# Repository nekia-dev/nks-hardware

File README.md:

# NkS — Placa portadora (carrier) · PROYECTO SOMNIA

**Nekia Systems S.L.** · Hardware del monitor de sueño NkS
*"Your Data, Your Device."*

Placa portadora para ESP32-S3 DevKitC-1 N16R8. Diseño "árbol de pascua apagado":
hardware mínimo, el valor está en el software.

---

## Estado

| Etapa | Estado |
|---|---|
| Hardware congelado | ✅ |
| Esquemático + ERC | ✅ 0 errores |
| Layout + DRC | ✅ 0 errores / 0 sin conectar |
| Gerbers | ✅ generados y verificados |
| Fabricación | ⏳ pendiente de pedido |
| Validación física | ⏳ pendiente (ver §Validación) |

---

## Datos de fabricación

| Parámetro | Valor |
|---|---|
| Dimensiones | **80 × 90 mm** (8 × 9 cm) |
| Capas | 2 (F.Cu / B.Cu) |
| Grosor | 1,6 mm (estándar) |
| Contorno | Rectangular |
| Plano de masa | GND en **ambas** caras |
| Pistas | 271 segmentos + 4 vías |
| Taladros | 80 (brocas 0,3 / 1,0 / 1,1 mm) |
| Ancho de pista | 0,2 mm (señal) |
| Componentes | 18 |

> El formato circular queda aplazado: el rectangular abarata el prototipo.

---

## Arquitectura

El ESP32-S3 DevKitC-1 **no va soldado**: se enchufa sobre dos tiras de pines
hembra 1×22 (`J2` = fila J1 del DevKit, `J3` = fila J3). Los sensores y
periféricos son módulos comerciales (breakouts) montados sobre headers.

**Consecuencia:** el fabricante entrega la placa **desnuda**. El montaje
(soldadura de headers y pasivos + enchufar el DevKit) es manual.

---

## Pinout congelado

| Bus | Señal | GPIO | Posición en header |
|---|---|---|---|
| I2S | WS | 11 | J2 pos. 17 |
| I2S | SCK | 12 | J2 pos. 18 |
| I2S | SD | 13 | J2 pos. 19 |
| SPI | MOSI | 15 | J2 pos. 8 |
| SPI | MISO | 16 | J2 pos. 9 |
| SPI | SCLK | 17 | J2 pos. 10 |
| SPI | CS | 18 | J2 pos. 11 |
| I2C | SDA | 8 | J2 pos. 12 |
| I2C | SCL | 9 | J2 pos. 15 |
| — | Botón on/off | 14 | J2 pos. 20 |
| — | LED estado | 21 | J3 pos. 18 |

**Alimentación:** 3V3 en J2 pos. 1–2 · GND en J2 pos. 22 y J3 pos. 1, 21, 22.

**Pines reservados (no usar):** strapping 0/3/45/46 · PSRAM octal (N16R8)
33–37 · USB nativo 19/20.

> El pinout físico J1/J3 procede de la guía oficial de Espressif del
> ESP32-S3-DevKitC-1 v1.1. **Verificar contra la placa real antes de soldar**
> (ver §Validación).

---

## BOM

| Ref | Componente | Interfaz | Notas |
|---|---|---|---|
| J2, J3 | Header 1×22 hembra ×2 | — | Zócalo del DevKit (paso 2,54 mm, filas a 22,86 mm) |
| A1 | INMP441 | I2S | Canal izquierdo — `L/R` → GND |
| A2 | INMP441 | I2S | Canal derecho — `L/R` → 3V3 |
| J1 | Lector microSD | SPI | — |
| U2 | RTC DS3231 + AT24C32 | I2C | 0x68 / 0x57 |
| U3 | SHT30 | I2C | 0x44 — temperatura + humedad |
| SW1 | Pulsador 6 mm | — | On/off, activo-bajo |
| R1 | 1 kΩ (0805) | — | Serie del LED |
| R2 | 10 kΩ (0805) | — | Pull-up del botón |
| D1 | LED (0805) | — | Indicador de estado |
| C1–C6 | 100 nF (0805) | — | Desacoplo + antirrebote |
| C7 | 10 µF (0805) | — | Bulk en el riel 3V3 |

**Aparte (no van en la placa):** ESP32-S3 DevKitC-1 N16R8, tarjeta microSD,
cable USB-C, carcasa.

Todas las huellas proceden de las **librerías estándar de KiCad**; el proyecto
no depende de librerías propias de footprints.

---

## Estructura del repositorio

```
nks.kicad_pro          Proyecto KiCad
nks.kicad_sch          Esquemático
nks.kicad_pcb          Placa (rutada, DRC limpio)
nks.kicad_sym          Biblioteca de símbolos del proyecto
sym-lib-table          Registro de la biblioteca de símbolos
docs/                  Informes de ingeniería
tools/nks-sch-gen/     Generador del esquemático en Rust
```

### Abrir el proyecto

Abrir `nks.kicad_pro` con **KiCad 10.0**. Los cuatro archivos de proyecto y
`sym-lib-table` deben estar en la misma carpeta.

---

## Validación (pendiente al recibir la placa)

El DRC a cero garantiza que la placa **coincide con el esquemático** y es
fabricable. **No** garantiza que el mapeo de pines del DevKit sea correcto.

1. **Continuidad con multímetro** (placa desnuda): comprobar que cada pad de
   los módulos pita con la posición esperada de J2/J3. Prioridad: I2C, I2S, SPI.
2. **Alimentación**: 3V3 y GND presentes en cada módulo antes de montar nada.
3. **Bloque a bloque**: alimentación → I2C (¿responde el RTC en 0x68?) → I2S →
   microSD. No montar todo de golpe.

---

## Decisiones de diseño registradas

- **2× INMP441 en estéreo** por el truco `L/R`: comparten los tres pines I2S sin
  GPIO adicionales. Habilita separar el ronquido propio del de la pareja.
- **SHT30 incorporado** como sensor de ambiente (temp + humedad). Restricción de
  layout: aislarlo térmicamente del DevKit y su regulador.
- **Sin conector USB-C propio**: se usa el USB-C nativo del DevKit.
- **BMP280 descartado**; **BH1750 aplazado**.
- **Plano de GND en ambas caras**: necesario porque D1 es SMD (su pad de masa
  vive solo en F.Cu) y el plano inferior quedó fragmentado por el rutado.

---

*Nekia Systems S.L. — CONFIDENCIAL*

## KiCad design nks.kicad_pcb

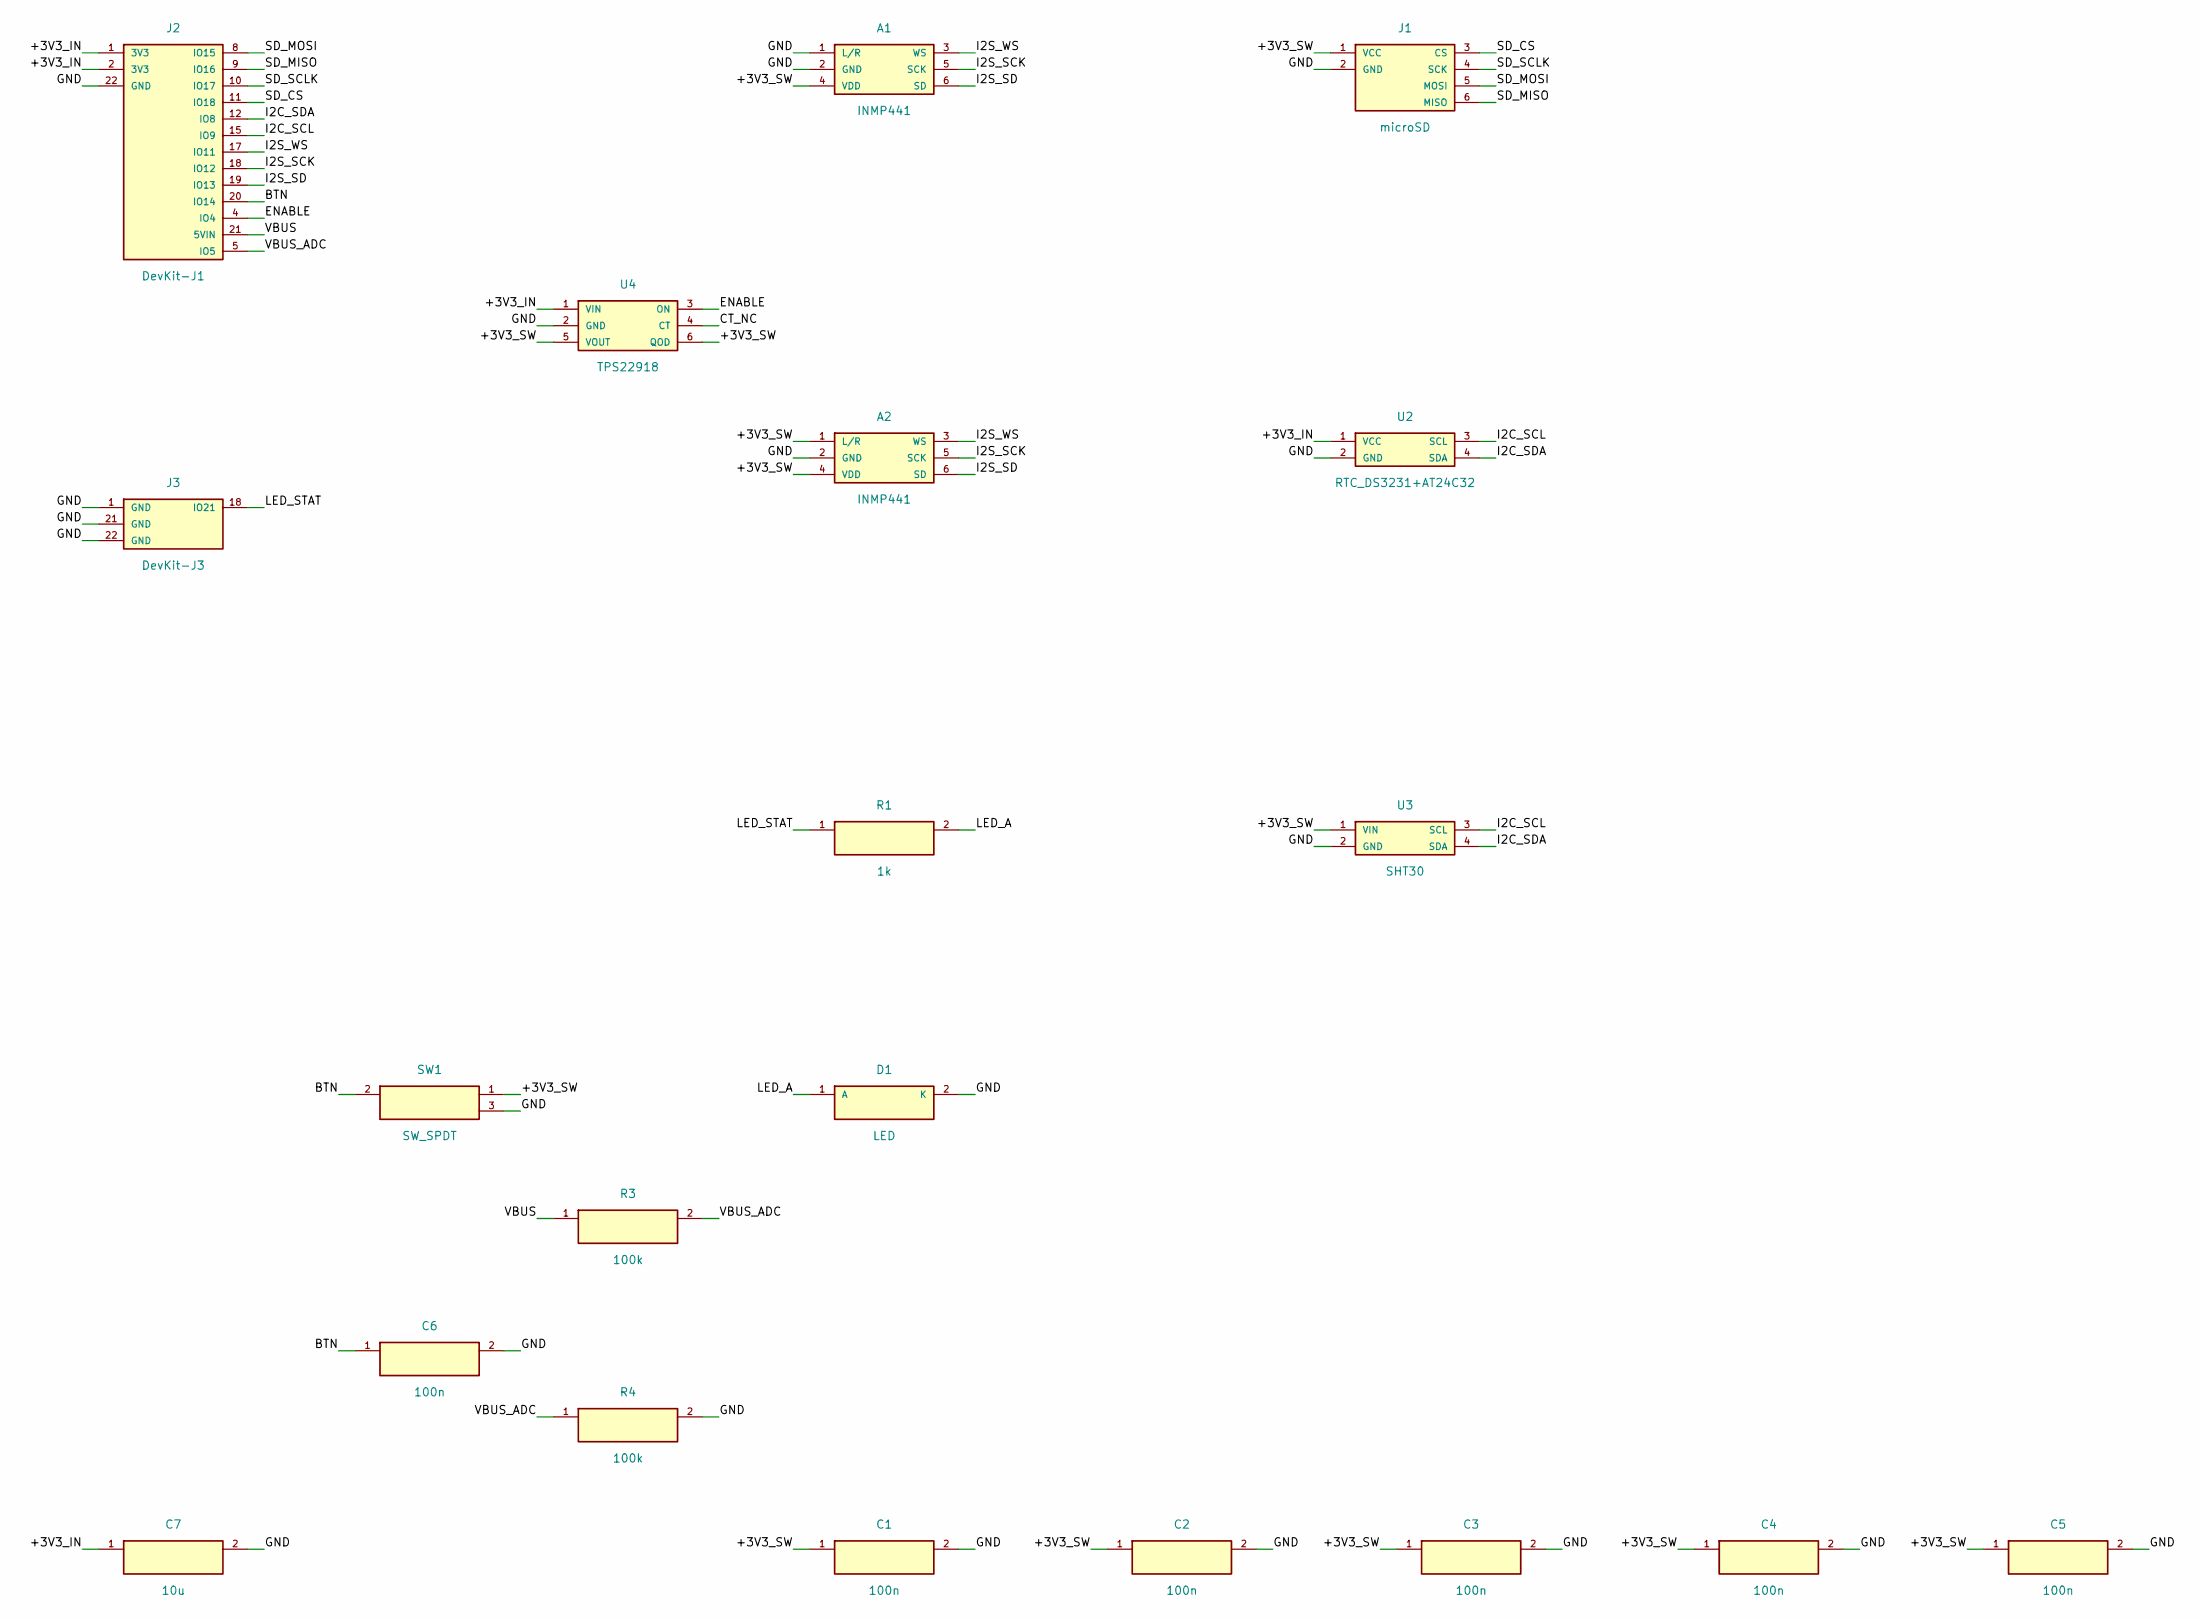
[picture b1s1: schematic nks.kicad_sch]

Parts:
A1, A2: INMP441; PinHeader_2x03_P2.54mm_Vertical
C1, C2, C3, C4, C5, C6: 100n; C_0805_2012Metric
C7: 10u; C_0805_2012Metric
D1: LED; LED_0805_2012Metric
J1: microSD; PinHeader_1x06_P2.54mm_Vertical
J2: DevKit-J1; PinHeader_1x22_P2.54mm_Vertical
J3: DevKit-J3; PinHeader_1x22_P2.54mm_Vertical
R1: 1k; R_0805_2012Metric
R3, R4: 100k; R_0805_2012Metric
SW1: SW_SPDT; SS12D00
U2: RTC_DS3231+AT24C32; PinHeader_1x06_P2.54mm_Vertical
U3: SHT30; PinHeader_1x04_P2.54mm_Vertical
U4: TPS22918; SOT-23-6

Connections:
/+3V3_IN: C7.1, J2.1 (3V3), J2.2 (3V3), U2.1 (VCC), U4.1 (VIN)
/+3V3_SW: A1.4 (VDD), A2.1 (L/R), A2.4 (VDD), C1.1, C2.1, C3.1, C4.1, C5.1, J1.1 (VCC), SW1.1, U3.1 (VIN), U4.5 (VOUT), U4.6 (QOD)
/BTN: C6.1, J2.20 (IO14), SW1.2
/CT_NC: U4.4 (CT)
/ENABLE: J2.4 (IO4), U4.3 (ON)
/GND: A1.1 (L/R), A1.2 (GND), A2.2 (GND), C1.2, C2.2, C3.2, C4.2, C5.2, C6.2, C7.2, D1.2 (K), J1.2 (GND), J2.22 (GND), J3.1 (GND), J3.21 (GND), J3.22 (GND), R4.2, SW1.3, U2.2 (GND), U3.2 (GND), U4.2 (GND)
/I2C_SCL: J2.15 (IO9), U2.3 (SCL), U3.3 (SCL)
/I2C_SDA: J2.12 (IO8), U2.4 (SDA), U3.4 (SDA)
/I2S_SCK: A1.5 (SCK), A2.5 (SCK), J2.18 (IO12)
/I2S_SD: A1.6 (SD), A2.6 (SD), J2.19 (IO13)
/I2S_WS: A1.3 (WS), A2.3 (WS), J2.17 (IO11)
/LED_A: D1.1 (A), R1.2
/LED_STAT: J3.18 (IO21), R1.1
/SD_CS: J1.3 (CS), J2.11 (IO18)
/SD_MISO: J1.6 (MISO), J2.9 (IO16)
/SD_MOSI: J1.5 (MOSI), J2.8 (IO15)
/SD_SCLK: J1.4 (SCK), J2.10 (IO17)
/VBUS: J2.21 (5VIN), R3.1
/VBUS_ADC: J2.5 (IO5), R3.2, R4.1

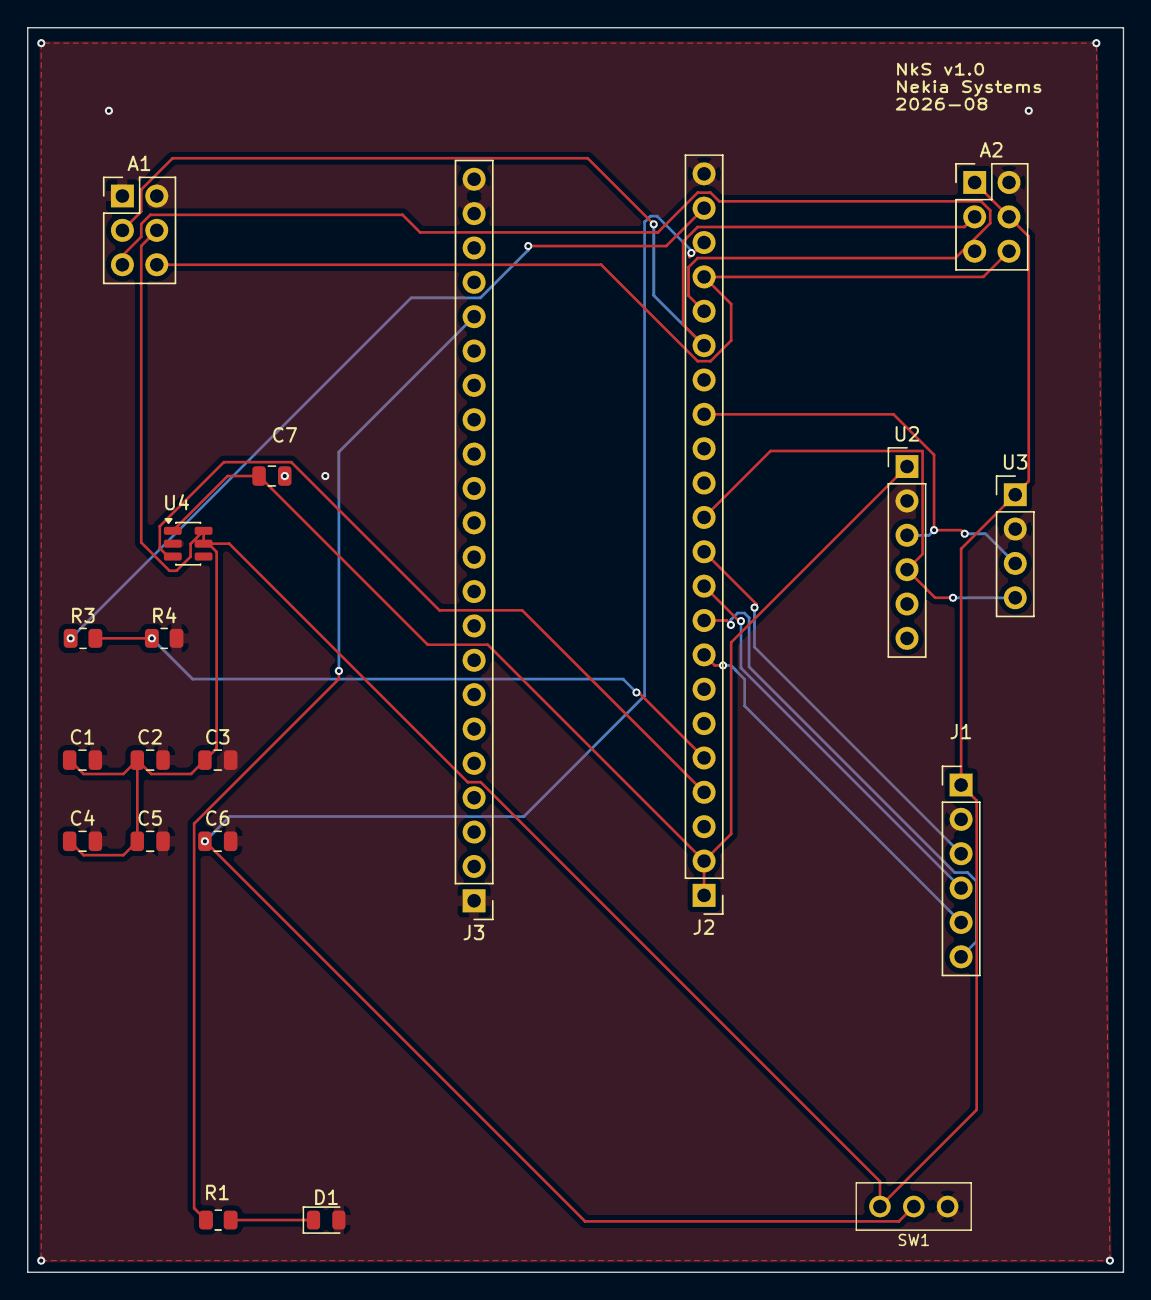
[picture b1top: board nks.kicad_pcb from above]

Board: 2 copper layers, 81.0 x 92.0 mm, 20 parts (0 on the bottom side), 18 nets.

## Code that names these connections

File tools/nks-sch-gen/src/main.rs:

mod kicad;
use kicad::{Component, Elec, Pin, Schematic, Side};

fn p_in(num: &str, name: &str, net: &str) -> Pin { Pin::new(num, name, Side::Left, Elec::PowerIn, net) }
fn p_out(num: &str, name: &str, net: &str) -> Pin { Pin::new(num, name, Side::Left, Elec::PowerOut, net) }
fn sig(num: &str, name: &str, net: &str) -> Pin { Pin::new(num, name, Side::Right, Elec::Passive, net) }
fn gpio(num: &str, name: &str, net: &str) -> Pin { Pin::new(num, name, Side::Right, Elec::Bidi, net) }
fn pas_l(num: &str, name: &str, net: &str) -> Pin { Pin::new(num, name, Side::Left, Elec::Passive, net) }
fn pas_r(num: &str, name: &str, net: &str) -> Pin { Pin::new(num, name, Side::Right, Elec::Passive, net) }

const HDR6: &str = "Connector_PinHeader_2.54mm:PinHeader_1x06_P2.54mm_Vertical";
const HDR4: &str = "Connector_PinHeader_2.54mm:PinHeader_1x04_P2.54mm_Vertical";
const HDR22: &str = "Connector_PinHeader_2.54mm:PinHeader_1x22_P2.54mm_Vertical";
const HDR2X3: &str = "Connector_PinHeader_2.54mm:PinHeader_2x03_P2.54mm_Vertical";
const R0805: &str = "Resistor_SMD:R_0805_2012Metric";
const C0805: &str = "Capacitor_SMD:C_0805_2012Metric";
const LED0805: &str = "LED_SMD:LED_0805_2012Metric";
const SW_SPDT: &str = "nks:SS12D00";
const SOT236: &str = "Package_TO_SOT_SMD:SOT-23-6";

fn main() {
    let mut sch = Schematic::new("NkS - SOMNIA carrier");

    // DevKit = two stock 1x22 female headers it plugs into. Pin NUMBER = physical
    // position on the official J1/J3 header (DevKitC-1 v1.1). One driver per rail
    // (3V3 + GND power_out, rest passive) to avoid multiple-power-output ERC errors.
    // J1 header row:
    sch.add(Component::new("J2", "DevKit-J1", HDR22, 20.0, 20.0)
        .pin(p_out("1", "3V3", "+3V3_IN")).pin(pas_l("2", "3V3", "+3V3_IN")).pin(p_out("22", "GND", "GND"))
        .pin(gpio("8", "IO15", "SD_MOSI")).pin(gpio("9", "IO16", "SD_MISO"))
        .pin(gpio("10", "IO17", "SD_SCLK")).pin(gpio("11", "IO18", "SD_CS"))
        .pin(gpio("12", "IO8", "I2C_SDA")).pin(gpio("15", "IO9", "I2C_SCL"))
        .pin(gpio("17", "IO11", "I2S_WS")).pin(gpio("18", "IO12", "I2S_SCK"))
        .pin(gpio("19", "IO13", "I2S_SD")).pin(gpio("20", "IO14", "BTN"))
        .pin(gpio("4", "IO4", "ENABLE"))
        .pin(gpio("21", "5VIN", "VBUS"))
        .pin(gpio("5", "IO5", "VBUS_ADC")));    // J3 header row:
    
    sch.add(Component::new("J3", "DevKit-J3", HDR22, 20.0, 90.0)
        .pin(pas_l("1", "GND", "GND")).pin(pas_l("21", "GND", "GND")).pin(pas_l("22", "GND", "GND"))
        .pin(gpio("18", "IO21", "LED_STAT")));

    // Load switch: parte +3V3_IN -> +3V3_SW, gobernado por ENABLE (GPIO4).
    sch.add(Component::new("U4", "TPS22918", SOT236, 90.0, 60.0)
        .pin(p_in("1", "VIN", "+3V3_IN")).pin(p_in("2", "GND", "GND"))
        .pin(sig("3", "ON", "ENABLE")).pin(sig("4", "CT", "CT_NC"))
        .pin(p_out("5", "VOUT", "+3V3_SW")).pin(sig("6", "QOD", "+3V3_SW")));

    sch.add(Component::new("A1", "INMP441", HDR2X3, 130.0, 20.0)
        .pin(pas_l("1", "L/R", "GND")).pin(p_in("2", "GND", "GND"))
        .pin(sig("3", "WS", "I2S_WS")).pin(p_in("4", "VDD", "+3V3_SW"))
        .pin(sig("5", "SCK", "I2S_SCK")).pin(sig("6", "SD", "I2S_SD")));
    
    sch.add(Component::new("A2", "INMP441", HDR2X3, 130.0, 80.0)
        .pin(pas_l("1", "L/R", "+3V3_SW")).pin(p_in("2", "GND", "GND"))
        .pin(sig("3", "WS", "I2S_WS")).pin(p_in("4", "VDD", "+3V3_SW"))
        .pin(sig("5", "SCK", "I2S_SCK")).pin(sig("6", "SD", "I2S_SD")));


    sch.add(Component::new("J1", "microSD", HDR6, 210.0, 20.0)
        .pin(p_in("1", "VCC", "+3V3_SW")).pin(p_in("2", "GND", "GND"))
        .pin(sig("3", "CS", "SD_CS")).pin(sig("4", "SCK", "SD_SCLK")).pin(sig("5", "MOSI", "SD_MOSI")).pin(sig("6", "MISO", "SD_MISO")));

    sch.add(Component::new("U2", "RTC_DS3231+AT24C32", HDR6, 210.0, 80.0)
        .pin(p_in("1", "VCC", "+3V3_IN")).pin(p_in("2", "GND", "GND"))
        .pin(sig("3", "SCL", "I2C_SCL")).pin(sig("4", "SDA", "I2C_SDA")));

    sch.add(Component::new("U3", "SHT30", HDR4, 210.0, 140.0)
        .pin(p_in("1", "VIN", "+3V3_SW")).pin(p_in("2", "GND", "GND"))
        .pin(sig("3", "SCL", "I2C_SCL")).pin(sig("4", "SDA", "I2C_SDA")));

    sch.add(Component::new("R1", "1k", R0805, 130.0, 140.0).pin(pas_l("1", "~", "LED_STAT")).pin(pas_r("2", "~", "LED_A")));
    sch.add(Component::new("D1", "LED", LED0805, 130.0, 180.0).pin(pas_l("1", "A", "LED_A")).pin(pas_r("2", "K", "GND")));

    sch.add(Component::new("SW1", "SW_SPDT", SW_SPDT, 60.0, 180.0)
    .pin(pas_l("2", "~", "BTN")).pin(pas_r("1", "~", "+3V3_SW")).pin(pas_r("3", "~", "GND")));

    sch.add(Component::new("C6", "100n", C0805, 60.0, 220.0).pin(pas_l("1", "~", "BTN")).pin(pas_r("2", "~", "GND")));

    for (r, x) in [("C1", 130.0), ("C2", 175.0), ("C3", 220.0), ("C4", 265.0), ("C5", 310.0)] {
        sch.add(Component::new(r, "100n", C0805, x, 250.0).pin(pas_l("1", "~", "+3V3_SW")).pin(pas_r("2", "~", "GND")));
    }
    sch.add(Component::new("C7", "10u", C0805, 20.0, 250.0).pin(pas_l("1", "~", "+3V3_IN")).pin(pas_r("2", "~", "GND")));

    // Divisor VBUS->ADC: vigila los 5V del USB (deteccion tiron de cable).
    // 5V -> R3(100k) -> nodo(VBUS_ADC) -> R4(100k) -> GND  => ~2.5V al ADC (GPIO5).
    sch.add(Component::new("R3", "100k", R0805, 90.0, 200.0)
        .pin(pas_l("1", "~", "VBUS")).pin(pas_r("2", "~", "VBUS_ADC")));
    sch.add(Component::new("R4", "100k", R0805, 90.0, 230.0)
        .pin(pas_l("1", "~", "VBUS_ADC")).pin(pas_r("2", "~", "GND")));



    let out = sch.render();
    std::fs::write("nks.kicad_sch", &out).expect("write .kicad_sch");

    let pro = format!(
        "{{\n  \"board\": {{ \"design_settings\": {{}} }},\n  \"meta\": {{ \"filename\": \"nks.kicad_pro\", \"version\": 1 }},\n  \"schematic\": {{}},\n  \"sheets\": [ [ \"{}\", \"Root\" ] ]\n}}\n",
        sch.root_uuid
    );
    std::fs::write("nks.kicad_pro", &pro).expect("write .kicad_pro");
    std::fs::write("nks.kicad_sym", sch.render_sym_lib()).expect("write .kicad_sym");
    std::fs::write("sym-lib-table", sch.render_sym_lib_table()).expect("write sym-lib-table");

    println!("wrote nks.kicad_sch ({} bytes) + project (stock footprints only)", out.len());
}
